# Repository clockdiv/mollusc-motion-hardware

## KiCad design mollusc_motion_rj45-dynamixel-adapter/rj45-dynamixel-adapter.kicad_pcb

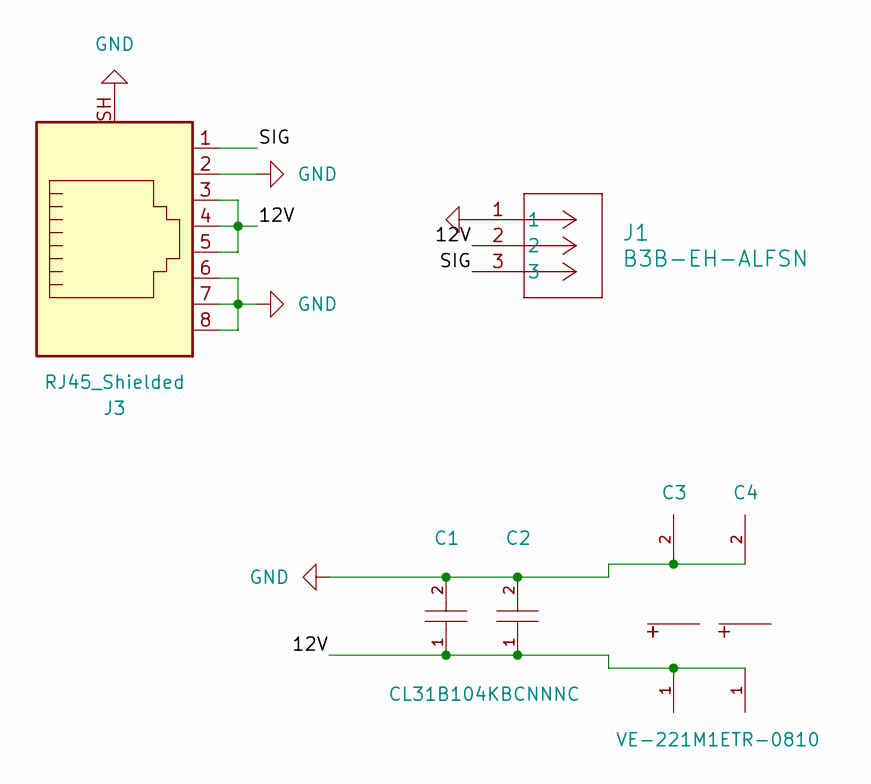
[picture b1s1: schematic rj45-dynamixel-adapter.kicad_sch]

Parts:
C1, C2: CL31B104KBCNNNC; C1206; LCSC C24497
C3, C4: VE-221M1ETR-0810; CAP-SMD_BD8.0-L8.3-W8.3-RD; LCSC C127967
J1: B3B-EH-ALFSN; CONN3_B3B-EH-ALFSN_JST
J3: RJ45_Shielded; RJ45_Conrad_1586526

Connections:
/12V: C1.1, C2.1, C3.1, C4.1, J1.2, J3.3, J3.4, J3.5
/SIG: J1.3, J3.1
GND: C1.2, C2.2, C3.2, C4.2, J1.1, J3.2, J3.6, J3.7, J3.8, J3.SH

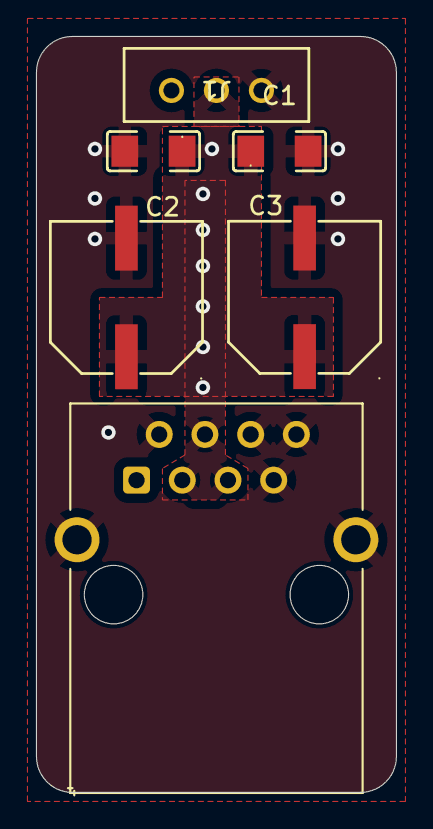
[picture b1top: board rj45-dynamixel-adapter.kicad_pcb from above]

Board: 4 copper layers, 20.0 x 42.0 mm, 6 parts (0 on the bottom side), 3 nets.

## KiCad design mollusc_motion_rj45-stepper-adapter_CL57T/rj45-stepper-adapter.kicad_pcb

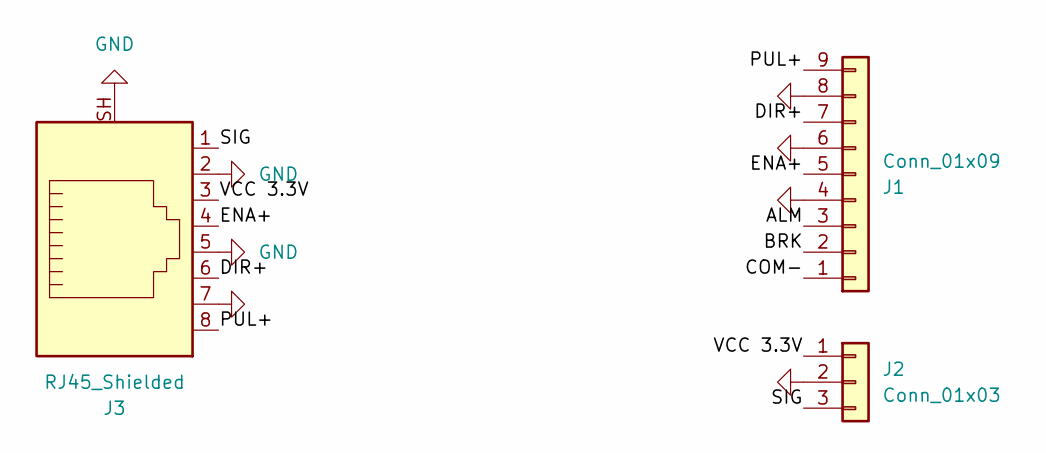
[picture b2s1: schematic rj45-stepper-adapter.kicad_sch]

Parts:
J1: Conn_01x09; Terminalblock_1x9_3.5mm
J2: Conn_01x03; PinHeader_1x03_P2.54mm_Vertical
J3: RJ45_Shielded; RJ45_Conrad_1586526

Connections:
/ALM: J1.3
/BRK: J1.2
/COM-: J1.1
/DIR+: J1.7, J3.6
/ENA+: J1.5, J3.4
/PUL+: J1.9, J3.8
/SIG: J2.3, J3.1
/VCC 3.3V: J2.1, J3.3
GND: J1.4, J1.6, J1.8, J2.2, J3.2, J3.5, J3.7, J3.SH

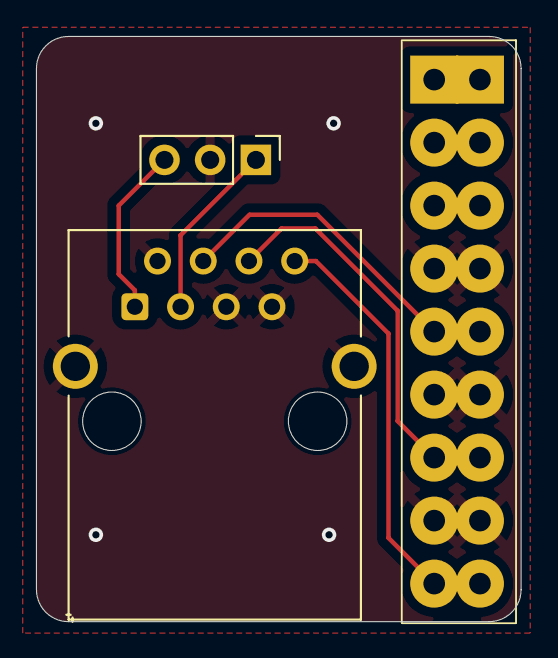
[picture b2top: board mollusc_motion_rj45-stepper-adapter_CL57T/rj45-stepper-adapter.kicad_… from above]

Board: 2 copper layers, 26.9 x 32.5 mm, 3 parts (0 on the bottom side), 6 nets.

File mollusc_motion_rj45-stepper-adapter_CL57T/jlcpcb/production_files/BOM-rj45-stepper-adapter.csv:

Comment,Designator,Footprint,LCSC
Conn_01x09,J1,Terminalblock_1x9_3.5mm,
Conn_01x03,J2,PinHeader_1x03_P2.54mm_Vertical,
RJ45_Shielded,J3,RJ45_Conrad_1586526,

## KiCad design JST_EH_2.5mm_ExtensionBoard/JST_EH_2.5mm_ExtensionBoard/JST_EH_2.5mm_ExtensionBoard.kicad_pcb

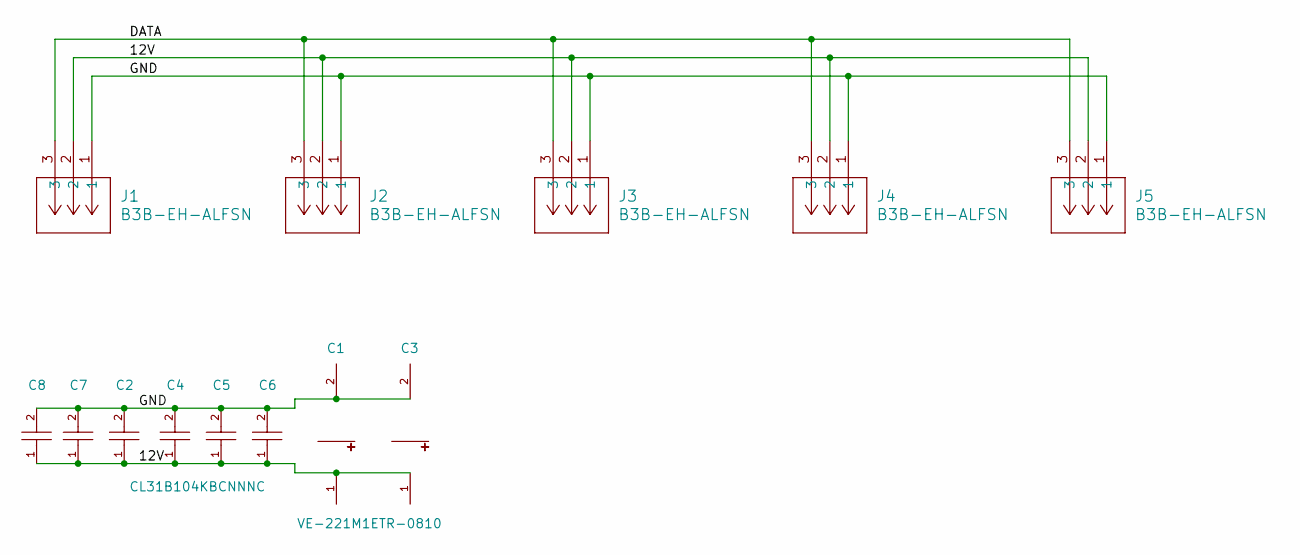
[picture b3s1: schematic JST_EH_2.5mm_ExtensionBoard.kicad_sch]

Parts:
C1, C3: VE-221M1ETR-0810; CAP-SMD_BD8.0-L8.3-W8.3-RD; LCSC C127967
C2, C4, C5, C6, C7, C8: CL31B104KBCNNNC; C1206; LCSC C24497
J1, J2, J3, J4, J5: B3B-EH-ALFSN; CONN3_B3B-EH-ALFSN_JST

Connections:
/12V: C1.1, C2.1, C3.1, C4.1, C5.1, C6.1, C7.1, C8.1, J1.2, J2.2, J3.2, J4.2, J5.2
/DATA: J1.3, J2.3, J3.3, J4.3, J5.3
/GND: C1.2, C2.2, C3.2, C4.2, C5.2, C6.2, C7.2, C8.2, J1.1, J2.1, J3.1, J4.1, J5.1

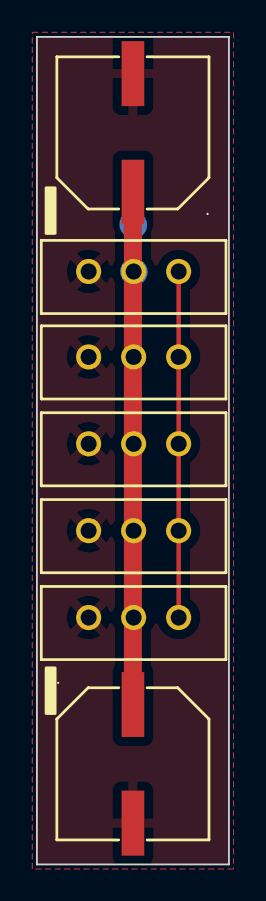
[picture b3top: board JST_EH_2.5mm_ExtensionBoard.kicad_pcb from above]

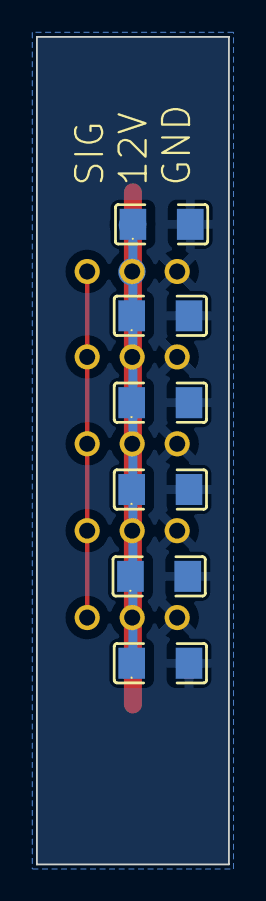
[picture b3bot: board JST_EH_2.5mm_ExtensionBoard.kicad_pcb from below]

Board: 2 copper layers, 10.7 x 46.0 mm, 13 parts (6 on the bottom side), 3 nets.

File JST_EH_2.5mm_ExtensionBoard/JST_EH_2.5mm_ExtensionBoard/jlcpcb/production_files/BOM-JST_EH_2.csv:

Comment,Designator,Footprint,LCSC
VE-221M1ETR-0810,"C1,C3",CAP-SMD_BD8.0-L8.3-W8.3-RD,C127967
CL31B104KBCNNNC,"C2,C4,C5,C6,C7,C8",C1206,C24497
B3B-EH-ALFSN,J5,CONN3_B3B-EH-ALFSN_JST,
B3B-EH-ALFSN,J4,CONN3_B3B-EH-ALFSN_JST,
B3B-EH-ALFSN,J3,CONN3_B3B-EH-ALFSN_JST,
B3B-EH-ALFSN,J2,CONN3_B3B-EH-ALFSN_JST,
B3B-EH-ALFSN,J1,CONN3_B3B-EH-ALFSN_JST,

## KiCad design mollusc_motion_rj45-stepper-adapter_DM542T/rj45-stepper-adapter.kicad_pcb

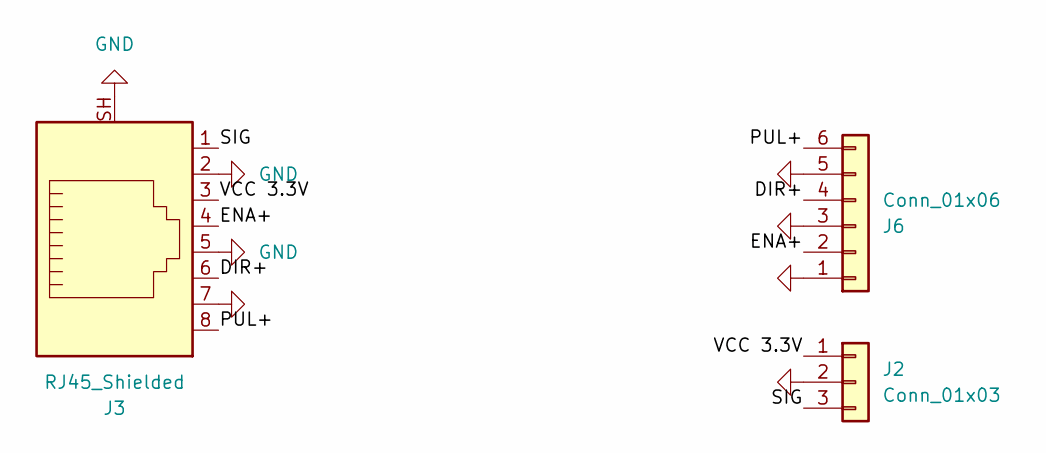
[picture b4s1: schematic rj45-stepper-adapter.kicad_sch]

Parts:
J2: Conn_01x03; PinHeader_1x03_P2.54mm_Vertical
J3: RJ45_Shielded; RJ45_Conrad_1586526
J6: Conn_01x06; Terminalblock_1x6_3.81mm

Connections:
/DIR+: J3.6, J6.4
/ENA+: J3.4, J6.2
/PUL+: J3.8, J6.6
/SIG: J2.3, J3.1
/VCC 3.3V: J2.1, J3.3
GND: J2.2, J3.2, J3.5, J3.7, J3.SH, J6.1, J6.3, J6.5

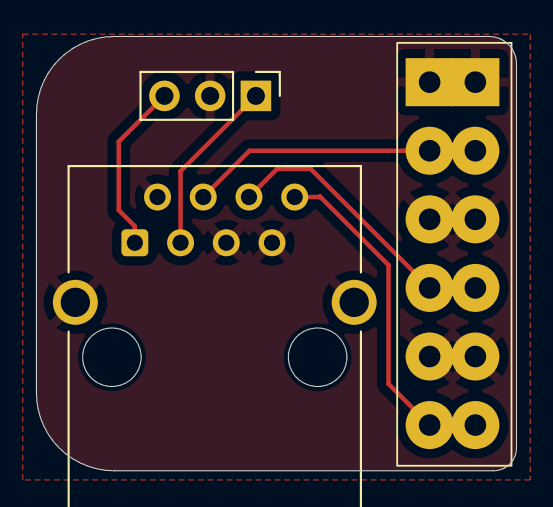
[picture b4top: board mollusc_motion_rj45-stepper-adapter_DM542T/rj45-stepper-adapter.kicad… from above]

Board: 2 copper layers, 26.7 x 24.1 mm, 3 parts (0 on the bottom side), 6 nets.

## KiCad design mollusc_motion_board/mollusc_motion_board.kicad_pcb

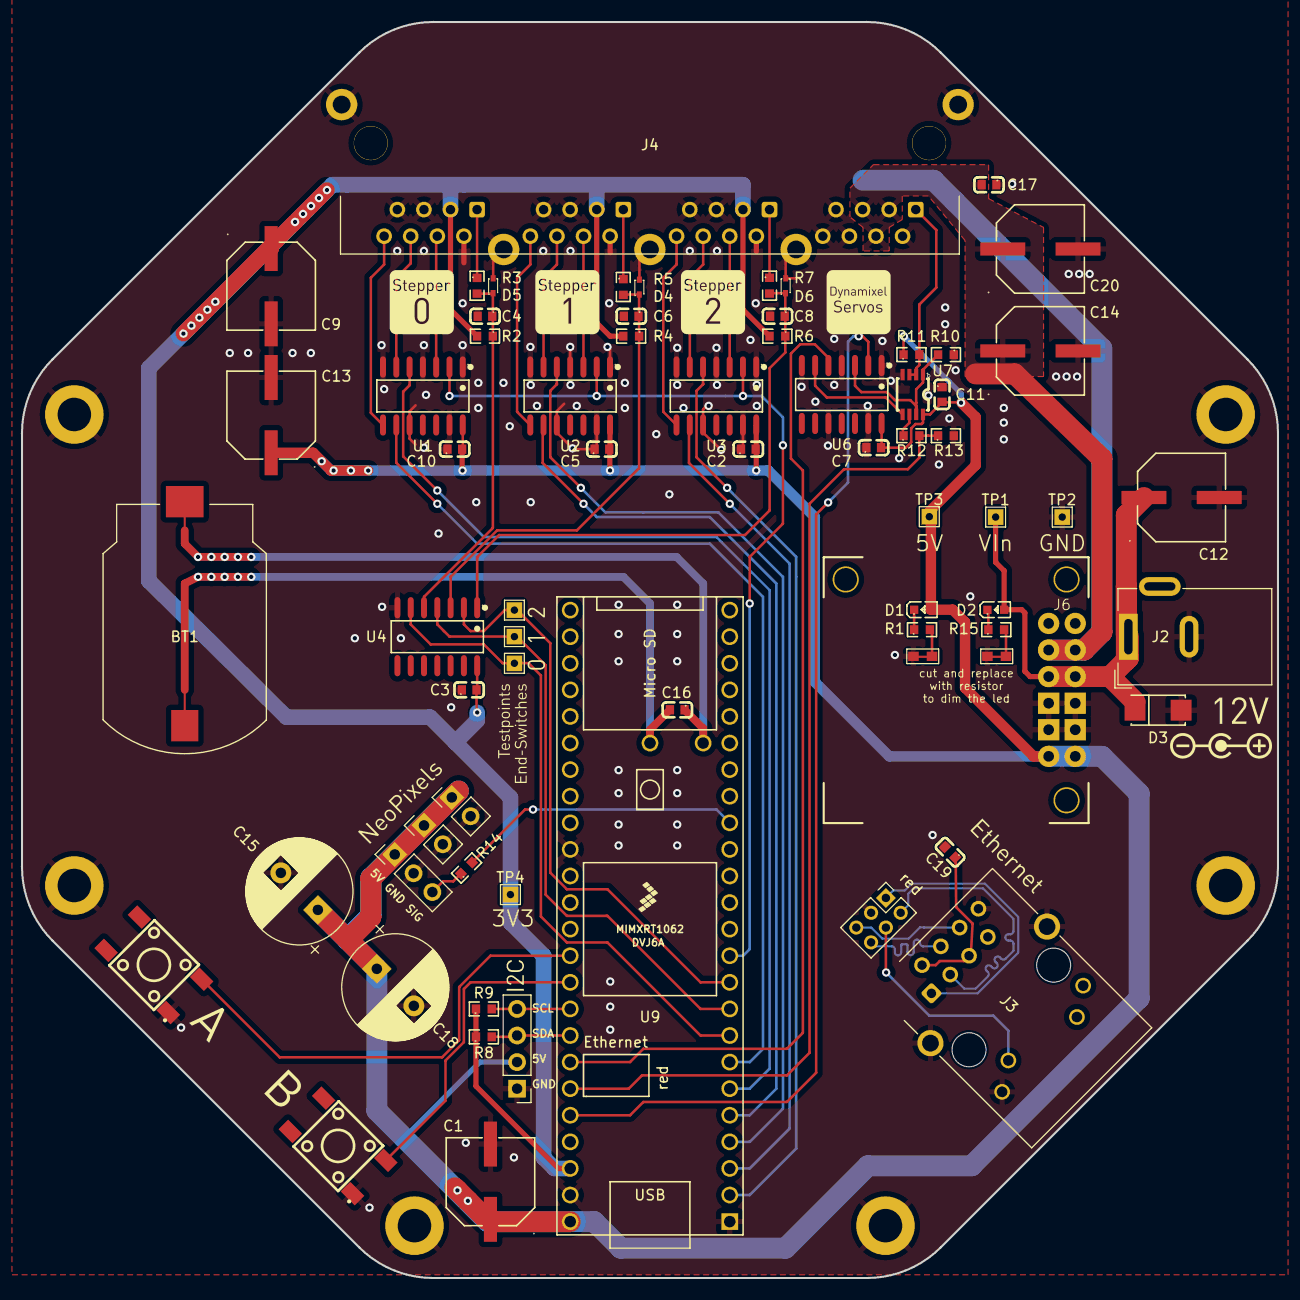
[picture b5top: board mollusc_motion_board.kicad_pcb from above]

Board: 4 copper layers, 120.0 x 120.0 mm, 75 parts (0 on the bottom side), 55 nets.

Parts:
BT1: Battery_Cell; BAT_S8421-45R
C1, C9, C12, C13, C14, C20: 220uF 35V; CAP-SMD_BD8.0-L8.3-W8.3-LS9.9-FD
C2, C3, C4, C5, C6, C7, C8, C10, C11, C16, C17, C19: 0.1uF 50V; C0603
C15, C18: 1000uF 25V; CP_Radial_D10.0mm_P5.00mm
CB1, CB2: CircuitBreaker_1P_closed; CircuitBreaker_0603_closed
D1, D2: LED; LED0603-RD
D3: SMAJ14A; SMA_L4.3-W2.6-LS5.1-RD
D4, D5, D6: ESD5Z5_0T1G; SOD-523F_L1.2-W0.8-LS1.7-RD
H1, H2, H3, H4, H5, H6: MountingHole; MountingHole_3.2mm_M3_DIN965_Pad
J1: NP Power+Sig; PinHeader_1x03_P2.54mm_Vertical
J2: Barrel_Jack_Switch 12V; BarrelJack_Wuerth_6941xx301002
J3: RJ45_LED_Shielded; RJ45_Cetus_J1B1211CCD_Horizontal
J4: RJ45 x4; RJ45_x4
J5: Conn_01x06_Pin; PinHeader_2x03_P2.00mm_Vertical
J6: D36V50F5; Pololu_5V_5.5A_Step-Down_Voltage_Regulator_D36V50F5
J7, J8: NP Power; PinHeader_1x02_P2.54mm_Vertical
J_I2C1: Conn_01x04_Pin; PinHeader_1x04_P2.54mm_Vertical
R1: 220; R0603
R2, R4, R6, R10, R11: 10k; R0603
R3, R5, R7, R8, R9: 1k; R0603
R12: 1.8k; R0603
R13: 3.3k; R0603
R14: 470; R0603
R15: 510; R0603
TP1: TP12V; TestPoint_THTPad_1.5x1.5mm_Drill0.7mm
TP2: TPGND; TestPoint_THTPad_1.5x1.5mm_Drill0.7mm
TP3: TP5V; TestPoint_THTPad_1.5x1.5mm_Drill0.7mm
TP4: TP3V3; TestPoint_THTPad_1.5x1.5mm_Drill0.7mm
TP_END_S1, TP_END_S2, TP_END_S3: TestPoint; TestPoint_THTPad_1.5x1.5mm_Drill0.7mm
U1, U2, U3, U6: SN74AHCT125N; SOIC-14_L8.7-W3.9-P1.27-LS6.0-BL
U4: 74HC14; SOIC-14_L8.7-W3.9-P1.27-LS6.0-BL
U5, U8: TSA063G60-250; KEY-SMD_4P-L6.1-W6.1-P4.50-LS9.0
U7: 74LVC2G241; SSOP-8_L3.0-W2.8-P0.65-LS4.0-BL
U9: Teensy4.1; Teensy41

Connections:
+3.3V: C3.2, C9.1, J4.B3, J4.C3, J4.D3, R2.2, R4.2, R6.2, R8.1, R9.1, TP4.1, U4.14 (VCC), U9.46 (3V3)
+5V: C1.1, C2.2, C5.2, C7.2, C10.2, C11.2, C13.1, C15.1, C18.1, D1.2 (A), J1.1, J6.1 (Vout), J7.1, J8.1, J_I2C1.2, R11.1, TP3.1, U1.14 (VCC), U2.14 (VCC), U3.14 (VCC), U6.14 (VCC), U7.8 (VCC), U9.48 (VIN)
+12V: C14.1, C17.2, C20.1, J4.A3, J4.A4, J4.A5, J6.4 (Vrp)
/BAT+: BT1.1 (+), C16.1, U9.50 (VBAT)
/BAT-: BT1.2 (-), C16.2, U9.52 (GND)
/DYN_DIRECTION: U6.2 (1A), U9.44 (22_A8_CTX1)
/DYN_RX: R12.2, R13.1, U9.43 (21_A7_RX5_BCLK1)
/DYN_TX: U6.5 (2A), U9.42 (20_A6_TX5_LRCLK1)
/DynamixelConnection/DYN_DATA: J4.A1, R11.2, U7.2, U7.3
/ETH_RX+: J3.4, J5.6
/ETH_RX-: J3.6, J5.5
/ETH_TX+: J3.1, J5.1
/ETH_TX-: J3.3, J5.2
/I2C_SCL: J_I2C1.3, R8.2, U9.41 (19_A5_SCL)
/I2C_SDA: J_I2C1.4, R9.2, U9.40 (18_A4_SDA)
/NEOPIXEL_SIG: R14.2, U9.16 (24_A10_TX6_SCL2)
/STEPPER_01_DIR: U1.5 (2A), U9.6 (4_BCLK2)
/STEPPER_01_END: TP_END_S1.1, U4.6, U9.8 (6_OUT1D)
/STEPPER_01_PULSE: U1.9 (3A), U9.7 (5_IN2)
/STEPPER_02_DIR: U2.5 (2A), U9.4 (2_OUT2)
/STEPPER_02_END: TP_END_S2.1, U4.4, U9.9 (7_RX2_OUT1A)
/STEPPER_02_PULSE: U2.9 (3A), U9.5 (3_LRCLK2)
/STEPPER_03_DIR: U3.5 (2A), U9.2 (0_RX1_CRX2_CS1)
/STEPPER_03_END: TP_END_S3.1, U4.2, U9.10 (8_TX2_IN1)
/STEPPER_03_PULSE: U3.9 (3A), U9.3 (1_TX1_CTX2_MISO1)
/Stepper01/DIR+: J4.D6, U1.6 (2Y)
/Stepper01/ENA+: J4.D4, U1.3 (1Y)
/Stepper01/PUL+: J4.D8, U1.8 (3Y)
/Stepper01/SIG: J4.D1, R3.1
/Stepper02/DIR+: J4.C6, U2.6 (2Y)
/Stepper02/ENA+: J4.C4, U2.3 (1Y)
/Stepper02/PUL+: J4.C8, U2.8 (3Y)
/Stepper02/SIG: J4.C1, R5.1
/Stepper03/DIR+: J4.B6, U3.6 (2Y)
/Stepper03/ENA+: J4.B4, U3.3 (1Y)
/Stepper03/PUL+: J4.B8, U3.8 (3Y)
/Stepper03/SIG: J4.B1, R7.1
/TEENSY_STEPPER_ENABLE: U1.2 (1A), U2.2 (1A), U3.2 (1A), U9.11 (9_OUT1C)
/Vin: C12.1, D2.2 (A), D3.1, J2.1, J6.3 (Vin), TP1.1
GND: C1.2, C2.1, C3.1, C4.2, C5.1, C6.2, C7.1, C8.2, C9.2, C10.1, C11.1, C12.2, C13.2, C14.2, C15.2, C17.1, C18.2, C19.2, C20.2, CB1.1, CB2.1, D3.2, D4.2 (A), D5.2 (A), D6.2 (A), H1.1, H2.1, H3.e, H4.1, H5.1, H6.1, J1.2, J2.2, J3.8, J3.9, J3.13, J4.A2, J4.A6, J4.A7, J4.A8, J4.B2, J4.B5, J4.B7, J4.C2, J4.C5, J4.C7, J4.D2, J4.D5, J4.D7, J4.GND, J5.3, J6.2 (GND), J7.2, J8.2, J_I2C1.1, R10.1, R13.2, TP2.1, U1.1 (1~OE), U1.4 (2~OE), U1.7 (GND), U1.10 (3~OE), U1.13 (4~OE), U2.1 (1~OE), U2.4 (2~OE), U2.7 (GND), U2.10 (3~OE), U2.13 (4~OE), U3.1 (1~OE), U3.4 (2~OE), U3.7 (GND), U3.10 (3~OE), U3.13 (4~OE), U4.7 (GND), U5.1, U6.1 (1~OE), U6.4 (2~OE), U6.7 (GND), U6.10 (3~OE), U6.13 (4~OE), U7.4 (GND), U8.1, U9.1 (GND), U9.34 (GND), U9.47 (GND)
unnamed: C19.1, J3.2, J3.5
unnamed: CB1.2, R15.2
unnamed: CB2.2, R1.2
unnamed: D1.1 (K), R1.1
unnamed: D2.1 (K), R15.1
unnamed: C6.1, D4.1 (C), R4.1, R5.2, U4.3
unnamed: C4.1, D5.1 (C), R2.1, R3.2, U4.5
unnamed: C8.1, D6.1 (C), R6.1, R7.2, U4.1
unnamed: J1.3, R14.1
unnamed: J3.10, J5.4
unnamed: R12.1, U7.6
unnamed: R10.2, U6.3 (1Y), U7.1, U7.7
unnamed: U6.6 (2Y), U7.5
unnamed: U8.3, U9.38 (16_A2_RX4_SCL1)
unnamed: U5.3, U9.39 (17_A3_TX4_SDA1)

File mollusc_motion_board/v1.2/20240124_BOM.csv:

"Source:","/Users/julian/Ernst Busch/02__PROJEKTE/20230930 mollusc motion Hardware/mollusc-motion-hardware/mollusc_motion_board/mollusc_motion_board.kicad_sch"
"Date:","2024 January 24, Wednesday 10:53:24"
"Tool:","Eeschema 7.0.5-0"
"Generator:","/Applications/KiCad/KiCad.app/Contents/SharedSupport/plugins/bom_csv_grouped_by_value.py"
"Component Count:","75"

"Collated Components:"

"Item","Qty","Reference(s)","Value","LibPart","Footprint","Datasheet","DNP","Category","Comment","DK_Datasheet_Link","DK_Detail_Page","Description","Digi-Key_PN","Family","JLCPCB Part #","LCSC","MPN","Manufacturer","Reseller","Status"
"1","1","BT1","Battery_Cell","Device:Battery_Cell","molluscmotion:BAT_S8421-45R","~","","","","","","","","","","","","","",""
"2","6","C1, C9, C12, C13, C14, C20","220uF 35V","Device:C_Polarized","molluscmotion:CAP-SMD_BD8.0-L8.3-W8.3-LS9.9-FD","~","","","","","","","","","C178594","","","","",""
"3","11","C2, C3, C4, C5, C6, C7, C8, C10, C11, C16, C17","0.1uF 50V ","Device:C","molluscmotion:C0603","~","","","place near SN74AHCT125N","","","","","","C14663","","","","",""
"4","2","C15, C18","1000uF 25V","Device:C_Polarized","Capacitor_THT:CP_Radial_D10.0mm_P5.00mm","~","","","place near Neopixel Connection","","","","","","","","","","",""
"5","1","C19","0.1uF 50V ","Device:C_Polarized","molluscmotion:C0603","~","","","","","","","","","C14663","","","","",""
"6","2","CB1, CB2","CircuitBreaker_1P_closed","clockdiv:CircuitBreaker_1P_closed","clockdiv:CircuitBreaker_0603_closed","~","","","","","","","","","","","","","",""
"7","2","D1, D2","LED","Device:LED","molluscmotion:LED0603-RD","~","","","","","","","","","C2286","","","","",""
"8","1","D3","SMAJ14A","molluscmotion:SMAJ14A_C908768","molluscmotion:SMA_L4.3-W2.6-LS5.1-RD","https://atta.szlcsc.com/upload/public/pdf/source/20180709/C2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","","","","","","","","","","C908768","","","",""
"9","3","D4, D5, D6","ESD5Z5_0T1G","molluscmotion:ESD5Z5_0T1G","molluscmotion:SOD-523F_L1.2-W0.8-LS1.7-RD","https://item.szlcsc.com/235389.html","","","","","","","","","","C82044","","","",""
"10","6","H1, H2, H3, H4, H5, H6","MountingHole","Mechanical:MountingHole","MountingHole:MountingHole_3.2mm_M3_DIN965_Pad","~","","","","","","","","","","","","","",""
"11","1","J1","NP Power+Sig","Connector:Conn_01x03_Pin","Connector_PinHeader_2.54mm:PinHeader_1x03_P2.54mm_Vertical","~","","","","","","","","","","","","","",""
"12","1","J2","Barrel_Jack_Switch 12V","Connector:Barrel_Jack_Switch","Connector_BarrelJack:BarrelJack_Wuerth_6941xx301002","~","","","","","","","","","","","","","",""
"13","1","J3","RJ45_LED_Shielded","Connector:RJ45_LED_Shielded","Connector_RJ:RJ45_Cetus_J1B1211CCD_Horizontal","~","","","","","","","","","","","","","",""
"14","1","J4","RJ45 x4","clockdiv:RJ45_x4","clockdiv:RJ45_x4","https://abracon.com/Magnetics/lan/ARJ14A.pdf","","","","","","","","","","","","","",""
"15","1","J5","Conn_01x06_Pin","Connector:Conn_01x06_Pin","Connector_PinHeader_2.00mm:PinHeader_2x03_P2.00mm_Vertical","~","","","","","","","","","","","","","",""
"16","1","J6","D36V50F5","clockdiv:Pololu_5V,_5.5A_Step-Down_Voltage_Regulator_D36V50F5","clockdiv:Pololu_5V_5.5A_Step-Down_Voltage_Regulator_D36V50F5","","","","","","","","","","","","","","https://eckstein-shop.de/Pololu-5V-55A-Step-Down-Voltage-Reg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",""
"17","2","J7, J8","NP Power","Connector:Conn_01x02_Pin","Connector_PinHeader_2.54mm:PinHeader_1x02_P2.54mm_Vertical","~","","","","","","","","","","","","","",""
"18","1","J_I2C1","Conn_01x04_Pin","Connector:Conn_01x04_Pin","Connector_PinHeader_2.54mm:PinHeader_1x04_P2.54mm_Vertical","~","","","","","","","","","","","","","",""
"19","1","R1","220","Device:R","molluscmotion:R0603","~","","","","","","","","","C22962","","","","",""
"20","5","R2, R4, R6, R10, R11","10k","Device:R","molluscmotion:R0603","~","","","","","","","","","C25804","","","","",""
"21","5","R3, R5, R7, R8, R9","1k","Device:R","molluscmotion:R0603","~","","","","","","","","","C21190","","","","",""
"22","1","R12","1.8k","Device:R","molluscmotion:R0603","~","","","","","","","","","C4177","","","","",""
"23","1","R13","3.3k","Device:R","molluscmotion:R0603","~","","","","","","","","","C22978","","","","",""
"24","1","R14","470","Device:R","molluscmotion:R0603","~","","","","","","","","","C23179","","","","",""
"25","1","R15","510","Device:R","molluscmotion:R0603","~","","","","","","","","","C23193","","","","",""
"26","1","TP1","TP12V","Connector:TestPoint","TestPoint:TestPoint_THTPad_1.5x1.5mm_Drill0.7mm","~","","","","","","","","","","","","","",""
"27","1","TP2","TPGND","Connector:TestPoint","TestPoint:TestPoint_THTPad_1.5x1.5mm_Drill0.7mm","~","","","","","","","","","","","","","",""
"28","1","TP3","TP5V","Connector:TestPoint","TestPoint:TestPoint_THTPad_1.5x1.5mm_Drill0.7mm","~","","","","","","","","","","","","","",""
"29","1","TP4","TP3V3","Connector:TestPoint","TestPoint:TestPoint_THTPad_1.5x1.5mm_Drill0.7mm","~","","","","","","","","","","","","","",""
"30","3","TP_END_S1, TP_END_S2, TP_END_S3","TestPoint","Connector:TestPoint","TestPoint:TestPoint_THTPad_1.5x1.5mm_Drill0.7mm","~","","","","","","","","","","","","","",""
"31","4","U1, U2, U3, U6","SN74AHCT125N","dk_Logic-Buffers-Drivers-Receivers-Transceivers:SN74AHCT125N","molluscmotion:SOIC-14_L8.7-W3.9-P1.27-LS6.0-BL","http://www.ti.com/general/docs/suppproductinfo.tsp?distId=10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","","Integrated Circuits (ICs)","","http://www.ti.com/general/docs/suppproductinfo.tsp?distId=10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","/product-detail/en/texas-instruments/SN74AHCT125N/296-4655-5-ND/375798","IC BUF NON-INVERT 5.5V 14DIP","296-4655-5-ND","Logic - Buffers, Drivers, Receivers, Transceivers","C155176","","SN74AHCT125N","Texas Instruments","","Active"
"32","1","U4","74HC14","74xx:74HC14","molluscmotion:SOIC-14_L8.7-W3.9-P1.27-LS6.0-BL","http://www.ti.com/lit/gpn/sn74HC14","","","","","","","","","C6820","","","","",""
"33","2","U5, U8","TSA063G60-250","molluscmotion:TSA063G60-250","molluscmotion:KEY-SMD_4P-L6.1-W6.1-P4.50-LS9.0","https://atta.szlcsc.com/upload/public/pdf/source/20181029/C2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","","","","","","","","","","C294566","","","",""
"34","1","U7","74LVC2G241","74xGxx:74LVC2G241","molluscmotion:SSOP-8_L3.0-W2.8-P0.65-LS4.0-BL","http://www.ti.com/lit/sg/scyt129e/scyt129e.pdf","","","","","","","","","C2676069","","","","",""
"35","1","U9","Teensy4.1","teensy:Teensy4.1","teensy:Teensy41","","","","","","","","","","","","","","",""

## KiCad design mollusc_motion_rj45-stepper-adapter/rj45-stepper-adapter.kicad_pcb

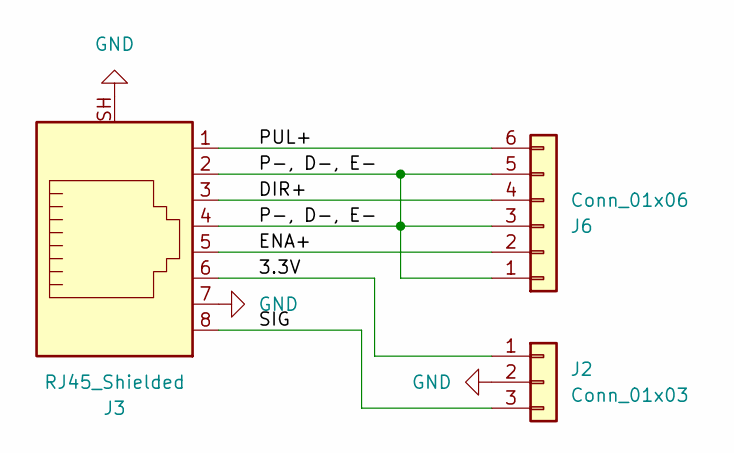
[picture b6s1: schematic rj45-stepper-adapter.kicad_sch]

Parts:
J2: Conn_01x03; PinHeader_1x03_P2.54mm_Vertical
J3: RJ45_Shielded; RJ45_Conrad_1586526
J6: Conn_01x06; Terminalblock_1x6_3.81mm

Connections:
/3.3V: J2.1, J3.6
/DIR+: J3.3, J6.4
/ENA+: J3.5, J6.2
/P-, D-, E-: J3.2, J3.4, J6.1, J6.3, J6.5
/PUL+: J3.1, J6.6
/SIG: J2.3, J3.8
GND: J2.2, J3.7, J3.SH

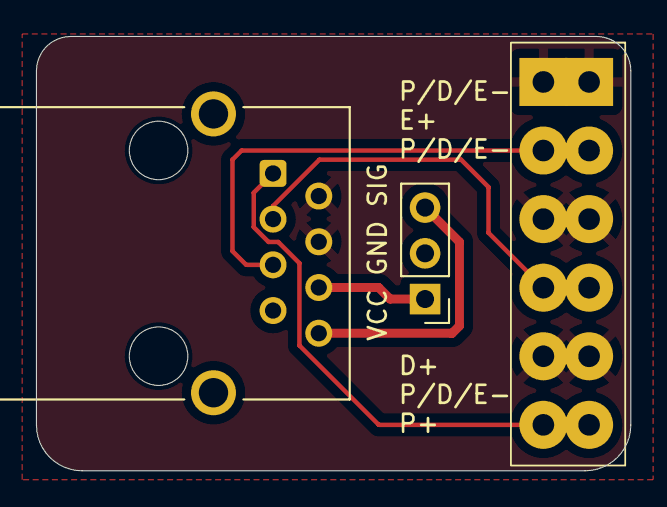
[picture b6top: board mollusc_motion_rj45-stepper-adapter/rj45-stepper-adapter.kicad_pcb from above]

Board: 2 copper layers, 33.0 x 24.1 mm, 3 parts (0 on the bottom side), 7 nets.

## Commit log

2023-10-11 initial commit
    Board v2.0 with Steppers and Dynamixels
    - bug with swapped connection on Stepper is resolved
2023-10-13 v3
    in production
2023-12-12 added mollusc motion logo to rj45 adapter
2023-12-29 adding BOM
    renaming to 'mollusc_motion'
2023-12-29 adding ethernet jack
2024-01-04 Board v2 wip
2024-01-05 PCB v1.2 Layout
2024-01-08 PCB v1.2
    v1.2, produced by JLCPCB
2024-01-26 backup pcb v1.2
    clean-up of the directory
2024-07-25 added JST-Header Extension Board
    tiny board to wire five Dynamixels in parallel
2024-07-25 Adapter for CL57T Stepper-Driver
2024-08-13 rj45-dynamixel-adapter
